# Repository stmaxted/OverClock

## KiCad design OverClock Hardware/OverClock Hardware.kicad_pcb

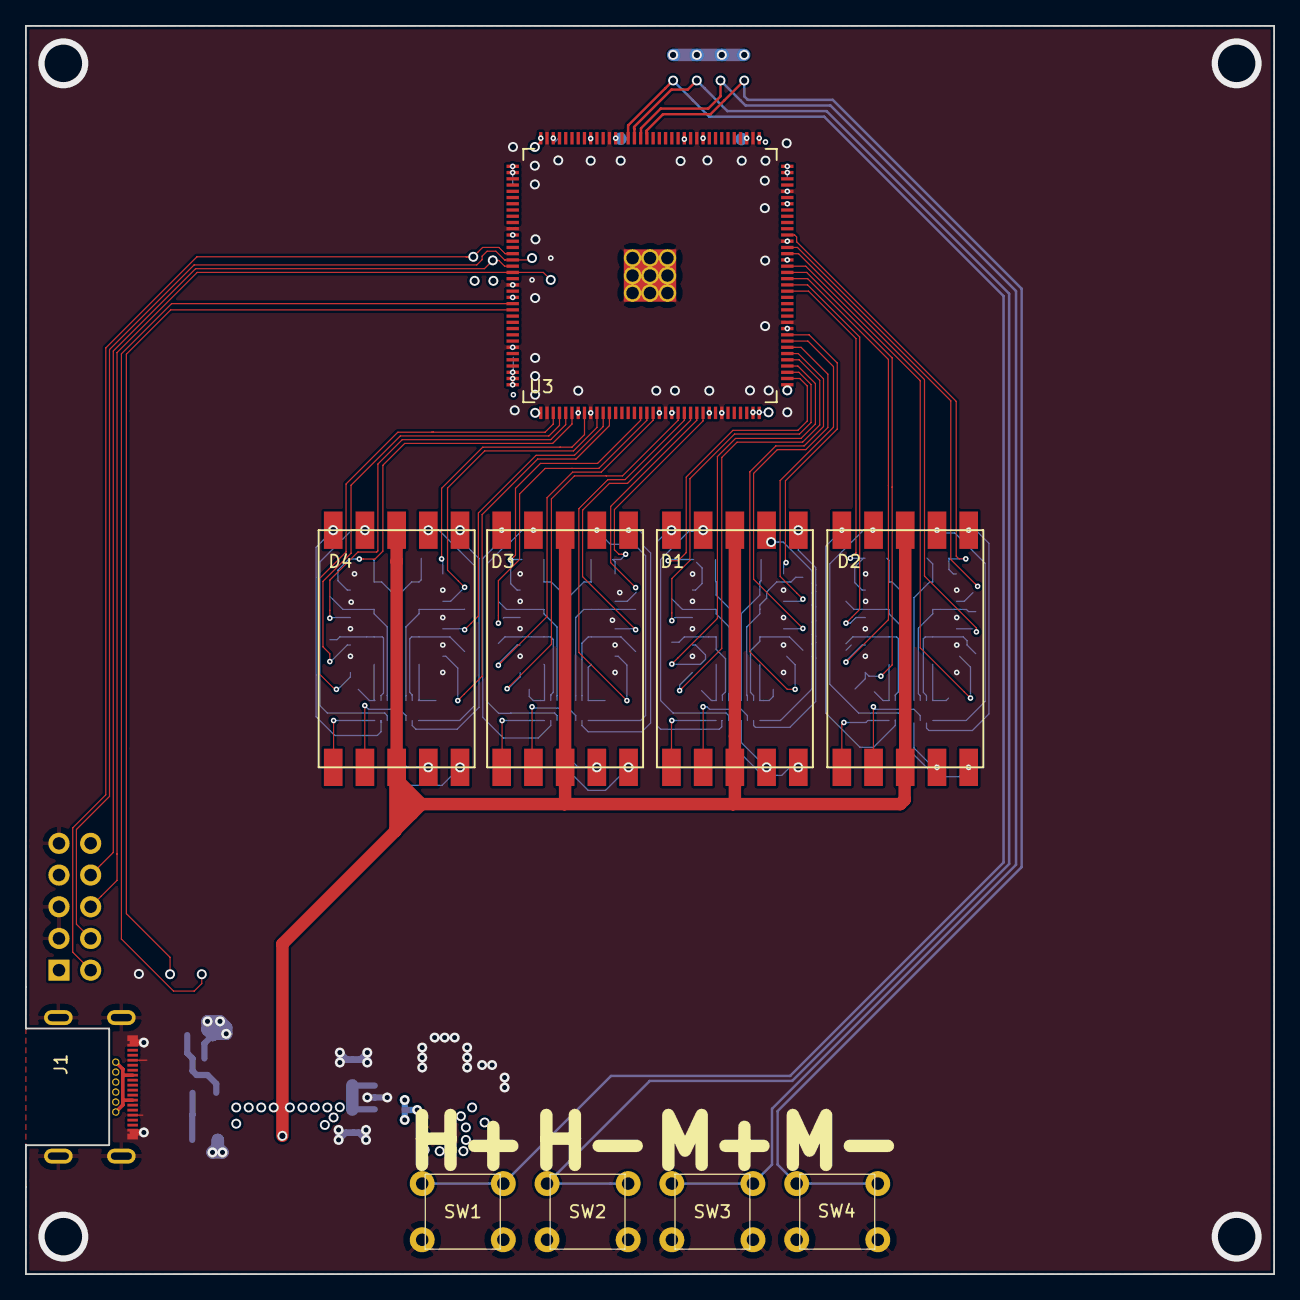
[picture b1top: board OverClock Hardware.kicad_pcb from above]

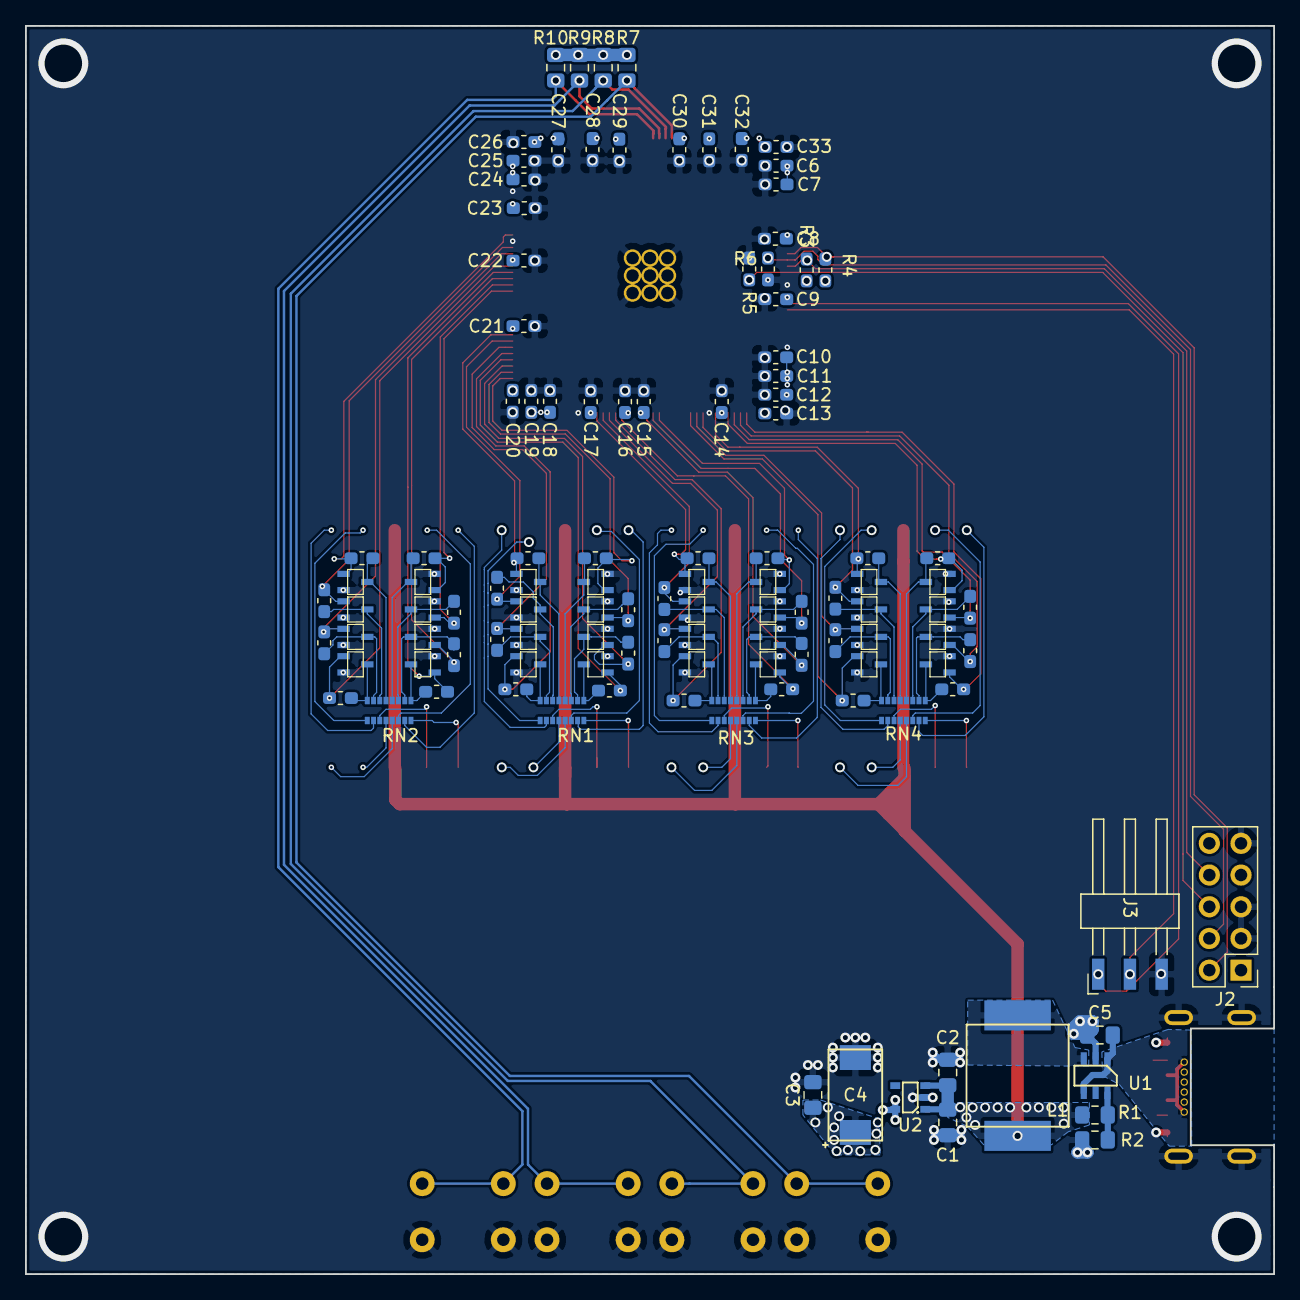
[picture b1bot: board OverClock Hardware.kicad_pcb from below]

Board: 4 copper layers, 100.0 x 100.0 mm, 126 parts (116 on the bottom side), 112 nets.

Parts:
C1, C2: 10uF; C_0805_2012Metric_Pad1.15x1.40mm_HandSolder
C3: 1uF; C_0805_2012Metric_Pad1.15x1.40mm_HandSolder
C4: 470uF; 293D
C5: 4.7uF; C_0805_2012Metric_Pad1.15x1.40mm_HandSolder
C6, C7, C8, C9, C10, C11, C12, C13, C14, C15, C16, C17, C18, C19, C20, C21, C22, C23, C24, C25, C26, C27, C28, C29, C30, C31, C32, C33: 10nF; C_0603_1608Metric_Pad1.05x0.95mm_HandSolder
D1, D2, D3, D4: DSM7TA56106T
J1: USB_C_Plug; Hirose_USB_C_Connector
J2: JTAG_HDR; PinHeader_2x05_P2.54mm_Vertical
J3: Conn_01x03_Female; Harwin_M20-89003xx_1x03_P2.54mm_Horizontal
L1: 2.2uH; IHLP3232
Q1, Q2, Q3, Q4, Q5, Q6, Q7, Q8, Q9, Q10, Q11, Q12, Q13, Q14, Q15, Q16, Q17, Q18, Q19, Q20, Q21, Q22, Q23, Q24, Q25, Q26, Q27, Q28, Q29, Q30, Q31, Q32: SOT-323
R1: 652K; R_0805_2012Metric_Pad1.15x1.40mm_HandSolder
R2: 100K; R_0805_2012Metric_Pad1.15x1.40mm_HandSolder
R3, R4, R5, R6, R11, R12, R13, R14, R15, R16, R17, R18, R19, R20, R21, R22, R23, R24, R25, R26, R27, R28, R29, R30, R31, R32, R33, R34, R35, R36, R37, R38, R39, R40, R41, R42: 1K; R_0603_1608Metric_Pad1.05x0.95mm_HandSolder
R7, R8, R9, R10: 1K; R_0805_2012Metric_Pad1.15x1.40mm_HandSolder
RN1, RN2, RN3, RN4: R_Pack08; 1506_Array
SW1, SW2, SW3, SW4: Switch_Momentary
U1: TLV62569; SOT23-6
U2: AP7365; SOT-23-5
U3: 10M02SCE144; QFP-144_EPAD_20x20_Pitch0.5mm

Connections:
+3V: C3.1, C4.1, C6.1, C7.1, C8.1, C9.1, C10.1, C11.1, C12.1, C13.1, C14.1, C15.1, C16.1, C17.1, C18.1, C19.1, C20.1, C21.1, C22.1, C23.1, C24.1, C25.1, C26.1, C27.1, C28.1, C29.1, C30.1, C31.1, C32.1, C33.1, R3.1, R4.1, R7.1, R8.1, R9.1, R10.1, U2.5, U3.1, U3.2, U3.12, U3.22, U3.34, U3.35, U3.36, U3.37, U3.43, U3.56, U3.58, U3.64, U3.71, U3.72, U3.73, U3.82, U3.93, U3.102, U3.107, U3.108, U3.109, U3.111, U3.118, U3.121, U3.132, U3.136, U3.142, U3.144
+4V: C1.1, C2.1, D1.3, D1.8, D2.3, D2.8, D3.3, D3.8, D4.3, D4.8, L1.2, R1.1, U2.1, U2.3
/FPGA Interfacing/H+: R7.2, SW1.1, SW1.3, U3.130
/FPGA Interfacing/H-: R8.2, SW2.1, SW2.3, U3.129
/FPGA Interfacing/M+: R9.2, SW3.1, SW3.3, U3.128
/FPGA Interfacing/M-: R10.2, SW4.1, SW4.3, U3.127
/FPGA Interfacing/Rx: J3.2, U3.24
/FPGA Interfacing/TCK: J2.4, R6.1, U3.16
/FPGA Interfacing/TDI: J2.8, R3.2, U3.17
/FPGA Interfacing/TDO: J2.6, R5.1, U3.18
/FPGA Interfacing/TMS: J2.2, R4.2, U3.15
/FPGA Interfacing/Tx: J3.1, U3.23
GND: C1.2, C2.2, C3.2, C4.2, C5.2, C6.2, C7.2, C8.2, C9.2, C10.2, C11.2, C12.2, C13.2, C14.2, C15.2, C16.2, C17.2, C18.2, C19.2, C20.2, C21.2, C22.2, C23.2, C24.2, C25.2, C26.2, C27.2, C28.2, C29.2, C30.2, C31.2, C32.2, C33.2, J1.A1, J1.A12, J1.B1, J1.B12, J1.S1, J1.S2, J1.S3, J1.S4, J1.S5, J1.S6, J2.3, J2.5, J2.9, J3.3, Q1.2, Q2.2, Q3.2, Q4.2, Q5.2, Q6.2, Q7.2, Q8.2, Q9.2, Q10.2, Q11.2, Q12.2, Q13.2, Q14.2, Q15.2, Q16.2, Q17.2, Q18.2, Q19.2, Q20.2, Q21.2, Q22.2, Q23.2, Q24.2, Q25.2, Q26.2, Q27.2, Q28.2, Q29.2, Q30.2, Q31.2, Q32.2, R2.2, R5.2, R6.2, SW1.2, SW1.4, SW2.2, SW2.4, SW3.2, SW3.4, SW4.2, SW4.4, U1.2, U2.2, U3.11, U3.20, U3.30, U3.38, U3.45, U3.57, U3.66, U3.83, U3.96, U3.104, U3.110, U3.119, U3.133, U3.143, U3.EPAD
unnamed: D1.1, RN1.12
unnamed: D1.2, RN1.13
unnamed: D1.4, RN1.14
unnamed: D1.5, RN1.9
unnamed: D1.6, RN1.15
unnamed: D1.7, RN1.16
unnamed: D1.9, RN1.11
unnamed: D1.10, RN1.10
unnamed: D2.1, RN2.12
unnamed: D2.2, RN2.13
unnamed: D2.4, RN2.14
unnamed: D2.5, RN2.9
unnamed: D2.6, RN2.15
unnamed: D2.7, RN2.16
unnamed: D2.9, RN2.11
unnamed: D2.10, RN2.10
unnamed: D3.1, RN3.12
unnamed: D3.2, RN3.13
unnamed: D3.4, RN3.14
unnamed: D3.5, RN3.9
unnamed: D3.6, RN3.15
unnamed: D3.7, RN3.16
unnamed: D3.9, RN3.11
unnamed: D3.10, RN3.10
unnamed: D4.1, RN4.12
unnamed: D4.2, RN4.13
unnamed: D4.4, RN4.14
unnamed: D4.5, RN4.9
unnamed: D4.6, RN4.15
unnamed: D4.7, RN4.16
unnamed: D4.9, RN4.11
unnamed: D4.10, RN4.10
unnamed: L1.1, U1.3
unnamed: Q1.1, R11.2, U3.78
unnamed: Q1.3, R11.1, RN1.1
unnamed: Q2.1, R12.2, U3.79
unnamed: Q2.3, R12.1, RN1.2
unnamed: Q3.1, R13.2, U3.80
unnamed: Q3.3, R13.1, RN1.3
unnamed: Q4.1, R14.2, U3.81
unnamed: Q4.3, R14.1, RN1.4
unnamed: Q5.1, R15.2, U3.74
unnamed: Q5.3, R15.1, RN1.5
unnamed: Q6.1, R16.2, U3.75
unnamed: Q6.3, R16.1, RN1.6
unnamed: Q7.1, R17.2, U3.76
unnamed: Q7.3, R17.1, RN1.7
unnamed: Q8.1, R18.2, U3.77
unnamed: Q8.3, R18.1, RN1.8
unnamed: Q9.1, R19.2, U3.92
unnamed: Q9.3, R19.1, RN2.1
unnamed: Q10.1, R20.2, U3.94
unnamed: Q10.3, R20.1, RN2.2
unnamed: Q11.1, R21.2, U3.95
unnamed: Q11.3, R21.1, RN2.3
unnamed: Q12.1, R22.2, U3.97
unnamed: Q12.3, R22.1, RN2.4
unnamed: Q13.1, R23.2, U3.88
unnamed: Q13.3, R23.1, RN2.5
unnamed: Q14.1, R24.2, U3.89
unnamed: Q14.3, R24.1, RN2.6
unnamed: Q15.1, R25.2, U3.90
unnamed: Q15.3, R25.1, RN2.7
unnamed: Q16.1, R26.2, U3.91
unnamed: Q16.3, R26.1, RN2.8
unnamed: Q17.1, R27.2, U3.60
unnamed: Q17.3, R27.1, RN3.1
unnamed: Q18.1, R28.2, U3.61
unnamed: Q18.3, R28.1, RN3.2
unnamed: Q19.1, R29.2, U3.62
unnamed: Q19.3, R29.1, RN3.3
unnamed: Q20.1, R30.2, U3.63
unnamed: Q20.3, R30.1, RN3.4
unnamed: Q21.1, R31.2, U3.53
unnamed: Q21.3, R31.1, RN3.5
unnamed: Q22.1, R32.2, U3.54
unnamed: Q22.3, R32.1, RN3.6
unnamed: Q23.1, R33.2, U3.55
unnamed: Q23.3, R33.1, RN3.7
unnamed: Q24.1, R34.2, U3.59
unnamed: Q24.3, R34.1, RN3.8
unnamed: Q25.1, R35.2, U3.48
unnamed: Q25.3, R35.1, RN4.1
unnamed: Q26.1, R36.2, U3.47
unnamed: Q26.3, R36.1, RN4.2
unnamed: Q27.1, R37.2, U3.46
unnamed: Q27.3, R37.1, RN4.3
unnamed: Q28.1, R38.2, U3.44
unnamed: Q28.3, R38.1, RN4.4
unnamed: Q29.1, R39.2, U3.42
unnamed: Q29.3, R39.1, RN4.5
unnamed: Q30.1, R40.2, U3.41
unnamed: Q30.3, R40.1, RN4.6
unnamed: Q31.1, R41.2, U3.40
unnamed: Q31.3, R41.1, RN4.7
unnamed: Q32.1, R42.2, U3.39
unnamed: Q32.3, R42.1, RN4.8
unnamed: R1.2, R2.1, U1.6
VBUS: C5.1, J1.A4, J1.A9, J1.B4, J1.B9, U1.1, U1.4

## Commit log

2019-01-29 Create Project overview
    Created overview document (some will call charter) to allow the reader to get up to speed with the project by reading a single document.
2019-01-29 Create FPGA Selection Document
    Created a document to document the selection process for selecting the correct FPGA.
2019-01-29 Chose FPGA and Update FPGA Selection Document
    Chose the FPGA (Intel MAX 10) that is in stock on Digikey
2019-01-29 Create KiCAD Project
    Created KiCAD project for hardware development
2019-02-02 Updated Project Overview and FPGA Selection Documents
    Added Power Supply section in Project Overivew Document.
    Added Backup FPGA in the same package in case I run out of logic elements.
2019-02-02 Calculated Current requirements for LED Displays
2019-02-06 Calculate Resistor Values and add Resistor Packs to Schematic
    Calculated the resistor values for 20mA through each LED segment.
    Selected a resistor pack/network.
    Added Resistor packs to KiCAD Schematic
2019-02-06 Chose Buck Converter and added necessary documumentation
2019-02-08 Changed Buck converter output voltage to 4V and selected LDO
    Changed the switching voltage to 4V to allow for better dropout on the LDO. Chose the Diodes Integrated AP7365 LDO and added datasheet.
2019-02-08 Added in power supply section
    Added a Buck converter to drop Vbus (5-20V) down to 4V for LEDs and the the 4V line is dropped further to 3V using a LDO to power the FPGA
2019-02-08 Moved Project to Multi-Sheet Design
2019-02-08 Added JTAG Header
    Added a JTAG header and interfaced it to the FPGA as per: page 16 https://www.intel.com/content/dam/www/programmable/us/en/pdfs/literature/hb/max-10/m10_guidelines.pdf
2019-02-08 Fix duplicate Pullup Resistor on JTAG Header.
    Fixed error in JTAG header pullup resistor where the TDI line had 2 pullups and teh TMS had none. Both pins now have one each.
2019-02-08 Added Decoupling strategy and started adding decoupling capacitors
2019-02-08 Added Decoupling Caps for FPGA core
2019-02-08 Interfaced Hours Digits to FPGA
2019-02-09 Interfaced minutes digits to FPGA and added time selection methods
    Interfaced the two 7 Segment displays used for displaying the minutes to the FPGA.
    Added 4 Tactile switches to increment/decrement the hours and minutes separately.
    Added a header to allow for setting of the time via UART.
2019-02-09 Completed Schematic and ran ERC
2019-02-09 Matched symbols to footprints and generated netlist
2019-02-10 Started to route out basic blocks
    - FPGA Decoupling Caps
    - 2 of the digit MOSFETS
    - Power supply
    - FPGA location
    - Digit locations
2019-02-15 Added Lessons Learned Document
    Added a document to track the lessons I have learned over the course of this project.
2019-02-15 Place and route Decoupling Capacitors
    Placed and routed all the decoupling capacitors for the FPGA. Created Top and bottom GND planes too for better signal integrity
2019-02-16 Completed Initial Routing
2019-02-18 Rerouted 7 Segment Displays
    Rearranged the displays for cleaner routing, also modified the schematic for some of the displays to allow for better routing.
2019-02-26 Added Functional Block DIagram to Schematic
2019-02-26 Cleaned up board to remove DRC Errors
2019-02-27 Created Quartus Prime project and began Writing Firmware
    - Created Quartus Prime Project
    - Created Top level entity VHDL file
    - Created 7 Segment DIsplay Decoder VHDL file
2019-03-02 Generated Internal Oscillator IP core and assigned Pins
    Generated the internal oscillator clock at 106MHz and assigned the I/O pins as per the hardware
